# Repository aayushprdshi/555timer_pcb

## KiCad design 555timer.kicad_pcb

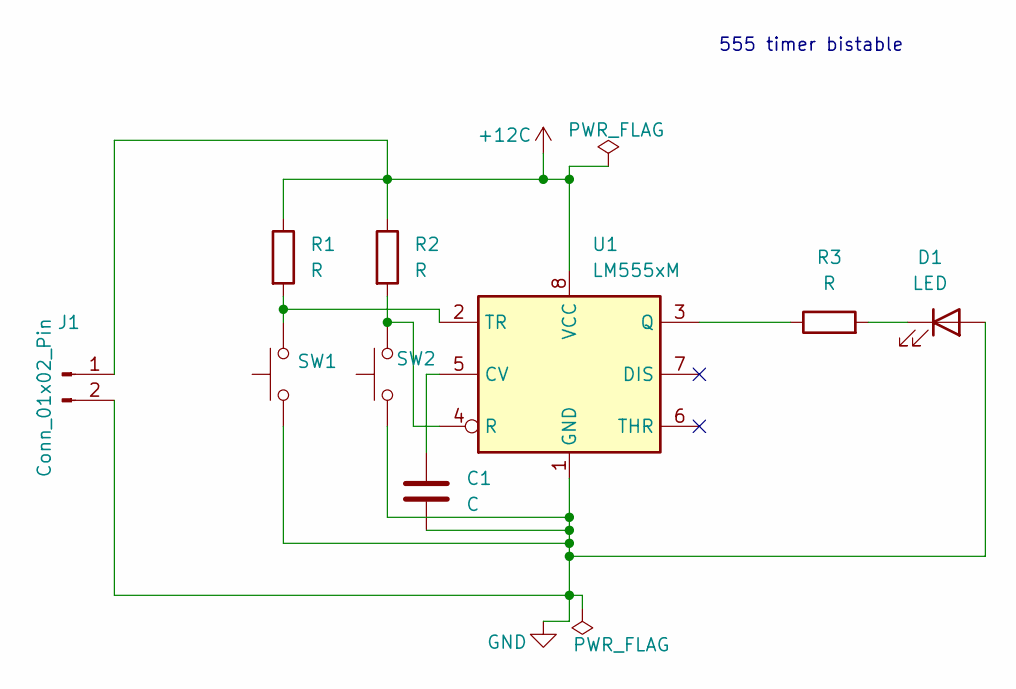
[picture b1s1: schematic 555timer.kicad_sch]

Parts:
C1: C; C_Disc_D10.5mm_W5.0mm_P5.00mm
D1: LED; LED_D5.0mm_Clear
J1: Conn_01x02_Pin; TE_440054-2_1x02_P2.00mm_Vertical
R1, R2, R3: R; R_Axial_DIN0411_L9.9mm_D3.6mm_P5.08mm_Vertical
SW1, SW2: SW_Push; SW_PUSH_6mm_H4.3mm
U1: LM555xM; SOIC-8_3.9x4.9mm_P1.27mm

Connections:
+12C: J1.1, R1.1, R2.1, U1.8 (VCC)
GND: C1.2, D1.2 (A), J1.2, SW1.1, SW2.1, U1.1 (GND)
unnamed: D1.1 (K), R3.2
unnamed: C1.1, U1.5 (CV)
unnamed: R3.1, U1.3 (Q)
unnamed: R2.2, SW2.2, U1.4 (R)
unnamed: R1.2, SW1.2, U1.2 (TR)

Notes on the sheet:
555 timer bistable

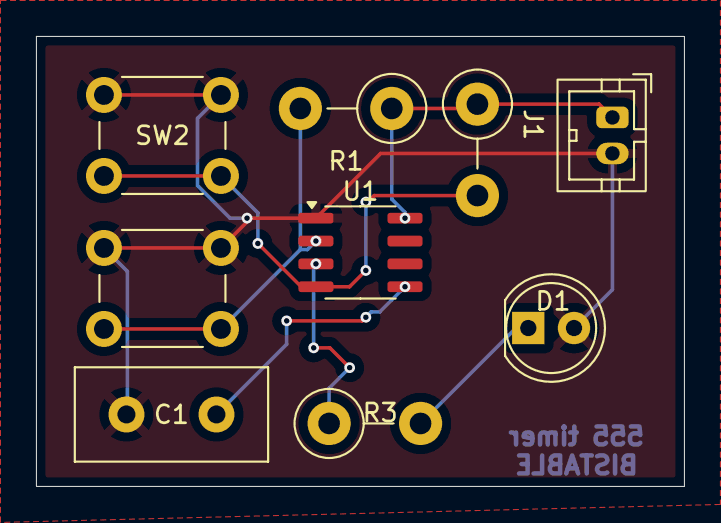
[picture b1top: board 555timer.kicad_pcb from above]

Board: 2 copper layers, 36.0 x 25.0 mm, 9 parts (0 on the bottom side), 7 nets.

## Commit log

2025-07-23 Add files via upload
    This project features a custom-designed PCB implementation of a bistable multivibrator circuit using the popular NE555 timer IC. In bistable mode, the 555 timer works as a flip-flop toggling its outp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
